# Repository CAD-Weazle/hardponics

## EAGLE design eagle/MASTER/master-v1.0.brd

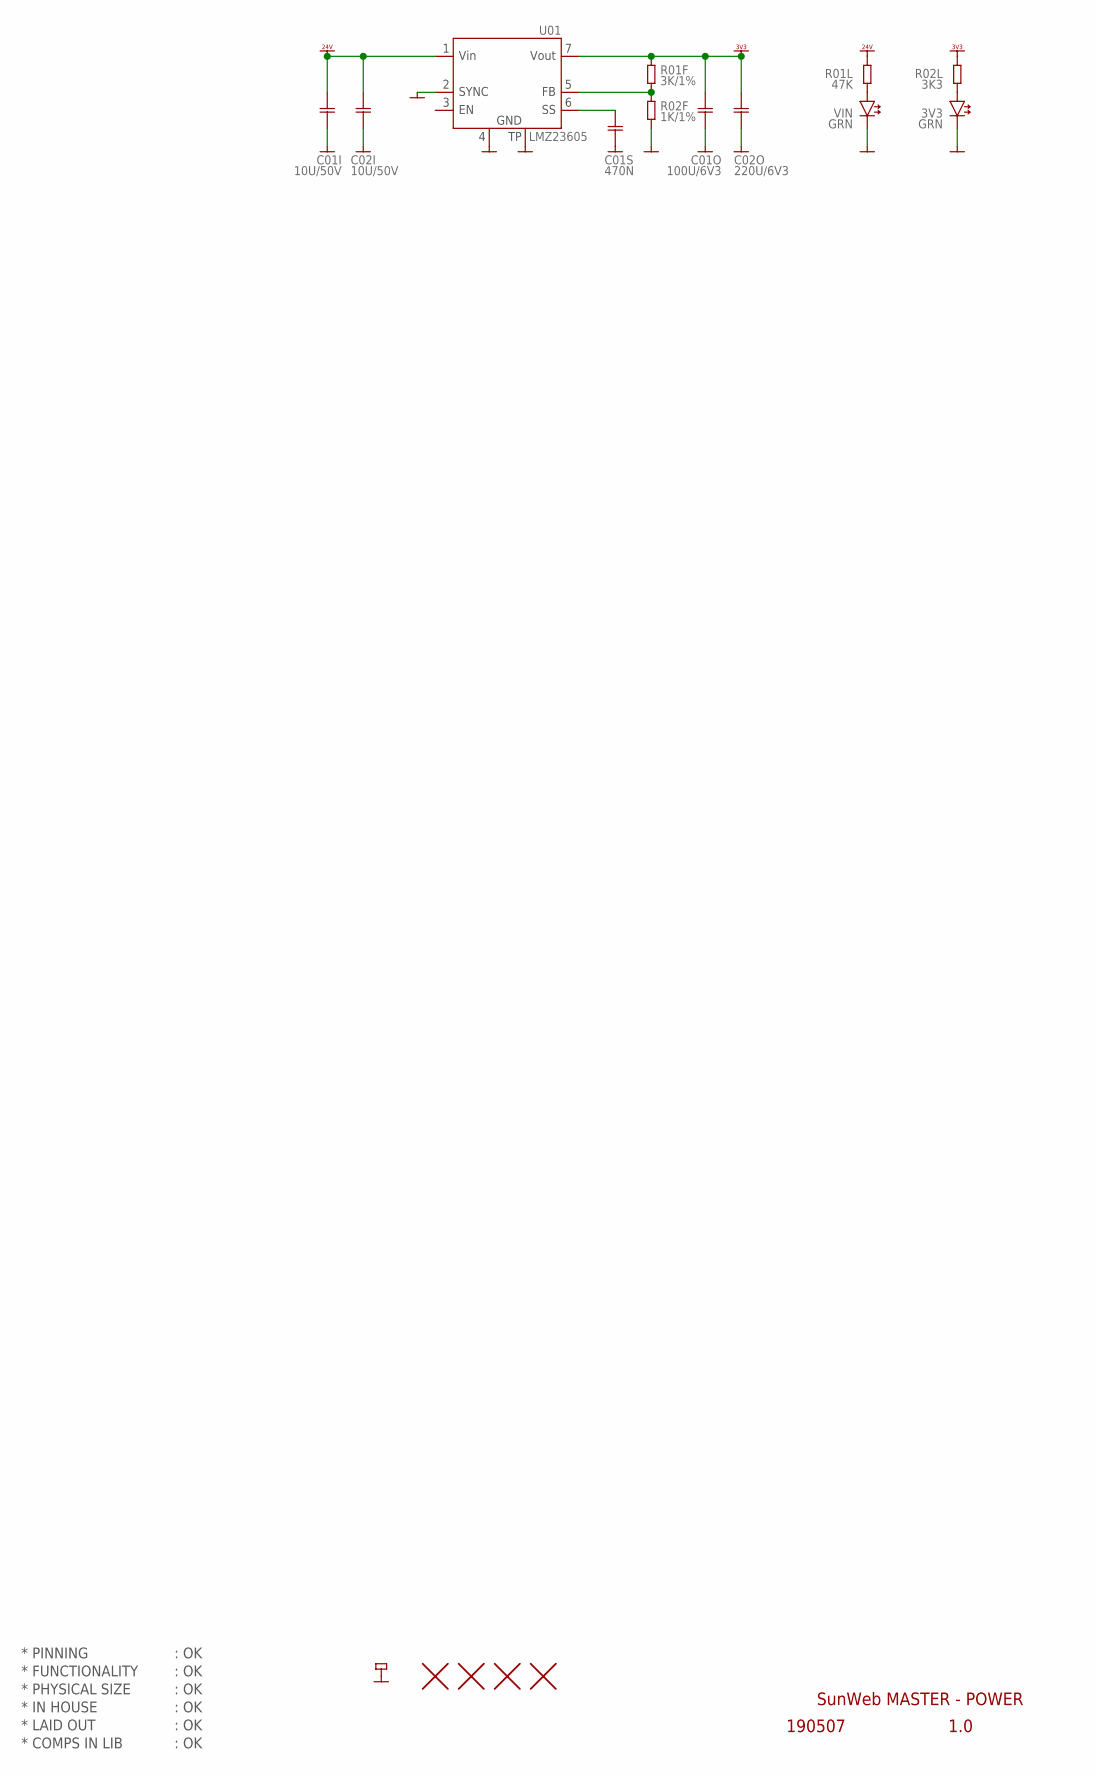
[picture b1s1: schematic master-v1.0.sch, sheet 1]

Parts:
3V3: GRN; LED_SMD_0603
C01I, C02I: 10U/50V; CAP1210
C01O: 100U/6V3; CAP1210
C01S: 470N; CAP0603
C02O: 220U/6V3; CAP2917
H1, H2, H3, H4: HOLE_NPTH_3.2MM
R01F: 3K/1%; RES0603@2
R01L: 47K; RES0603
R02F: 1K/1%; RES0603@2
R02L: 3K3; RES0603
TP2: PIN_GND; HOLE_PTH_1.8MM_SQR
U01: LMZ23605; TOPMOD-7
VIN: GRN; LED_SMD_0603

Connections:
GND: 3V3.C, C01I.2, C01O.2, C01S.2, C02I.2, C02O.2, R02F.1, TP2.1, U01.2 (2.SYNC), U01.4 (4.GND), U01.TP, VIN.C; also elsewhere on the board
unnamed: 3V3.A, R02L.2
unnamed: R01L.2, VIN.A
unnamed: C01S.1, U01.6 (6.SS)
unnamed: R01F.1, R02F.2, U01.5 (5.FB)
VDD_3V3: C01O.1, C02O.1, R01F.2, R02L.1, U01.7 (7.VOUT); also elsewhere on the board
VDD_24V: C01I.1, C02I.1, R01L.1, U01.1 (1.VIN); also elsewhere on the board

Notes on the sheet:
* PINNING
* FUNCTIONALITY
* PHYSICAL SIZE
* LAID OUT
* COMPS IN LIB
* IN HOUSE
SunWeb MASTER - POWER
190507
1.0
: OK

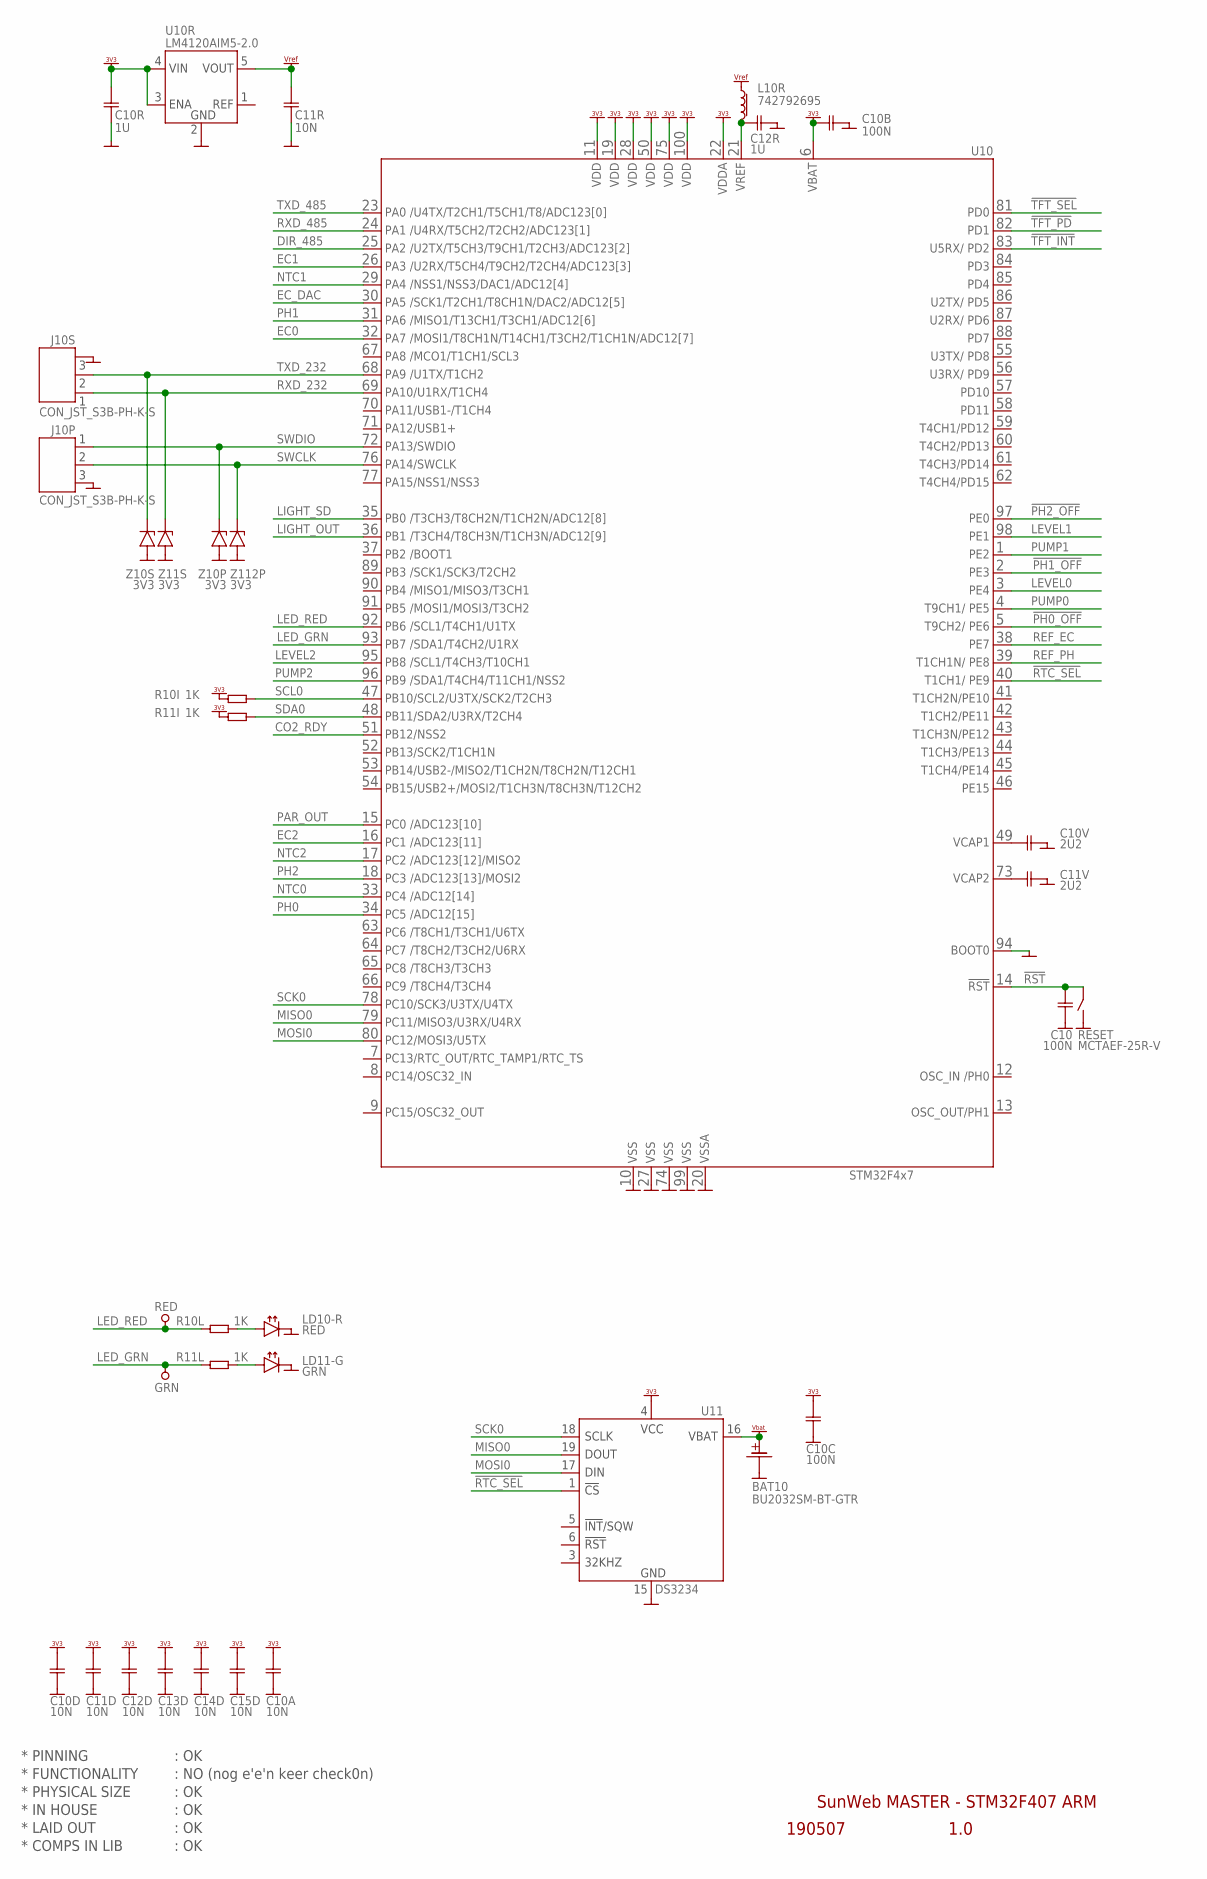
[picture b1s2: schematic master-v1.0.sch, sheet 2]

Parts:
BAT10: BU2032SM-BT-GTR
C10, C10B, C10C: 100N; CAP0603
C10A, C10D, C11D, C11R, C12D, C13D, C14D, C15D: 10N; CAP0603
C10R, C12R: 1U; CAP0603
C10V, C11V: 2U2; CAP0603
GRN: PIN_TEST; HOLE_PTH_0.8MM
J10P, J10S: CON_JST_S3B-PH-K-S
L10R: 742792695; L_0603
LD10-R: RED; LED_SMD_0603
LD11-G: GRN; LED_SMD_0603
R10I, R10L, R11I, R11L: 1K; RES0603
RED: PIN_TEST; HOLE_PTH_0.8MM
RESET: MCTAEF-25R-V; SWITCH_SMD_PBUTTON_2P
U10: STM32F407VG; LQFP100
U10R: LM4120AIM5-2.0; SOT23-5
U11: DS3234; SO20W
Z10P, Z10S, Z11S, Z112P: 3V3; ZENER_SOD80

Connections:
!PH0_OFF: U10.5 (5.PE6); also elsewhere on the board
!PH1_OFF: U10.2 (2.PE3); also elsewhere on the board
!PH2_OFF: U10.97 (97.PE0); also elsewhere on the board
!RST: C10.1, RESET.2 (3-4), U10.14 (14.!RST)
!RTC_SEL: U10.40 (40.PE9), U11.1 (1.CS)
!TFT_INT: U10.83 (83.PD2); also elsewhere on the board
!TFT_PD: U10.82 (82.PD1); also elsewhere on the board
!TFT_SEL: U10.81 (81.PD0); also elsewhere on the board
CO2_RDY: U10.51 (51.PB12); also elsewhere on the board
DIR_485: U10.25 (25.PA2); also elsewhere on the board
EC0: U10.32 (32.PA7); also elsewhere on the board
EC1: U10.26 (26.PA3); also elsewhere on the board
EC2: U10.16 (16.PC1); also elsewhere on the board
EC_DAC: U10.30 (30.PA5); also elsewhere on the board
GND: BAT10.2.- (2), C10.2, C10A.2, C10B.2, C10C.2, C10D.2, C10R.2, C10V.2, C11D.2, C11R.2, C11V.2, C12D.2, C12R.1, C13D.2, C14D.2, C15D.2, J10P.3, J10S.3, LD10-R.C, LD11-G.C, RESET.1 (1-2), U10.10 (10.VSS), U10.20 (20.VSSA), U10.27 (27.VSS), U10.74 (74.VSS), U10.94 (94.BOOT0), U10.99 (99.VSS), U10R.2 (2.GND), U11.2 (15.GND), U11.7 (15.GND), U11.8 (15.GND), U11.9 (15.GND), U11.10 (15.GND), U11.11 (15.GND), U11.12 (15.GND), U11.13 (15.GND), U11.14 (15.GND), U11.15 (15.GND), Z10P.1 (+), Z10S.1 (+), Z11S.1 (+), Z112P.1 (+); also elsewhere on the board
LED_GRN: GRN.1, R11L.1, U10.93 (93.PB7)
LED_RED: R10L.1, RED.1, U10.92 (92.PB6)
LEVEL0: U10.3 (3.PE4); also elsewhere on the board
LEVEL1: U10.98 (98.PE1); also elsewhere on the board
LEVEL2: U10.95 (95.PB8); also elsewhere on the board
LIGHT_OUT: U10.36 (36.PB1); also elsewhere on the board
LIGHT_SD: U10.35 (35.PB0); also elsewhere on the board
MISO0: U10.79 (79.PC11), U11.19 (19.DOUT); also elsewhere on the board
MOSI0: U10.80 (80.PC12), U11.17 (17.DIN); also elsewhere on the board
unnamed: C10V.1, U10.49 (49.VCAP1)
unnamed: C11V.1, U10.73 (73.VCAP2)
unnamed: LD11-G.A, R11L.2
unnamed: LD10-R.A, R10L.2
NTC0: U10.33 (33.PC4); also elsewhere on the board
NTC1: U10.29 (29.PA4); also elsewhere on the board
NTC2: U10.17 (17.PC2); also elsewhere on the board
PAR_OUT: U10.15 (15.PC0); also elsewhere on the board
PH0: U10.34 (34.PC5); also elsewhere on the board
PH1: U10.31 (31.PA6); also elsewhere on the board
PH2: U10.18 (18.PC3); also elsewhere on the board
PUMP0: U10.4 (4.PE5); also elsewhere on the board
PUMP1: U10.1 (1.PE2); also elsewhere on the board
PUMP2: U10.96 (96.PB9); also elsewhere on the board
REF_EC: U10.38 (38.PE7); also elsewhere on the board
REF_PH: U10.39 (39.PE8); also elsewhere on the board
RXD_232: J10S.1, U10.69 (69.PA10), Z11S.2 (-)
RXD_485: U10.24 (24.PA1); also elsewhere on the board
SCK0: U10.78 (78.PC10), U11.18 (18/20.SCLK), U11.20 (18/20.SCLK); also elsewhere on the board
SCL0: R10I.2, U10.47 (47.PB10); also elsewhere on the board
SDA0: R11I.2, U10.48 (48.PB11); also elsewhere on the board
SWCLK: J10P.2, U10.76 (76.PA14), Z112P.2 (-)
SWDIO: J10P.1, U10.72 (72.PA13), Z10P.2 (-)
TXD_232: J10S.2, U10.68 (68.PA9), Z10S.2 (-)
TXD_485: U10.23 (23.PA0); also elsewhere on the board
VBAT: BAT10.1.+ (1), U11.16 (16.VBAT)
VCC_VREF: C11R.1, L10R.1, U10R.5 (5.VOUT); also elsewhere on the board
VDD_3V3: C10A.1, C10B.1, C10C.1, C10D.1, C10R.1, C11D.1, C12D.1, C13D.1, C14D.1, C15D.1, R10I.1, R11I.1, U10.6 (6.VBAT), U10.11 (11.VDD), U10.19 (19.VDD), U10.22 (22.VDDA), U10.28 (28.VDD), U10.50 (50.VDD), U10.75 (75.VDD), U10.100 (100.VDD), U10R.3 (3.ENA), U10R.4 (4.VIN), U11.4 (4.VCC); also elsewhere on the board
VREF1: C12R.2, L10R.2, U10.21 (21.VREF+)

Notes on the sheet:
* PINNING
* FUNCTIONALITY
* PHYSICAL SIZE
* LAID OUT
* COMPS IN LIB
* IN HOUSE
: OK
SunWeb MASTER - STM32F407 ARM
190507
1.0
: NO (nog e'e'n keer check0n)

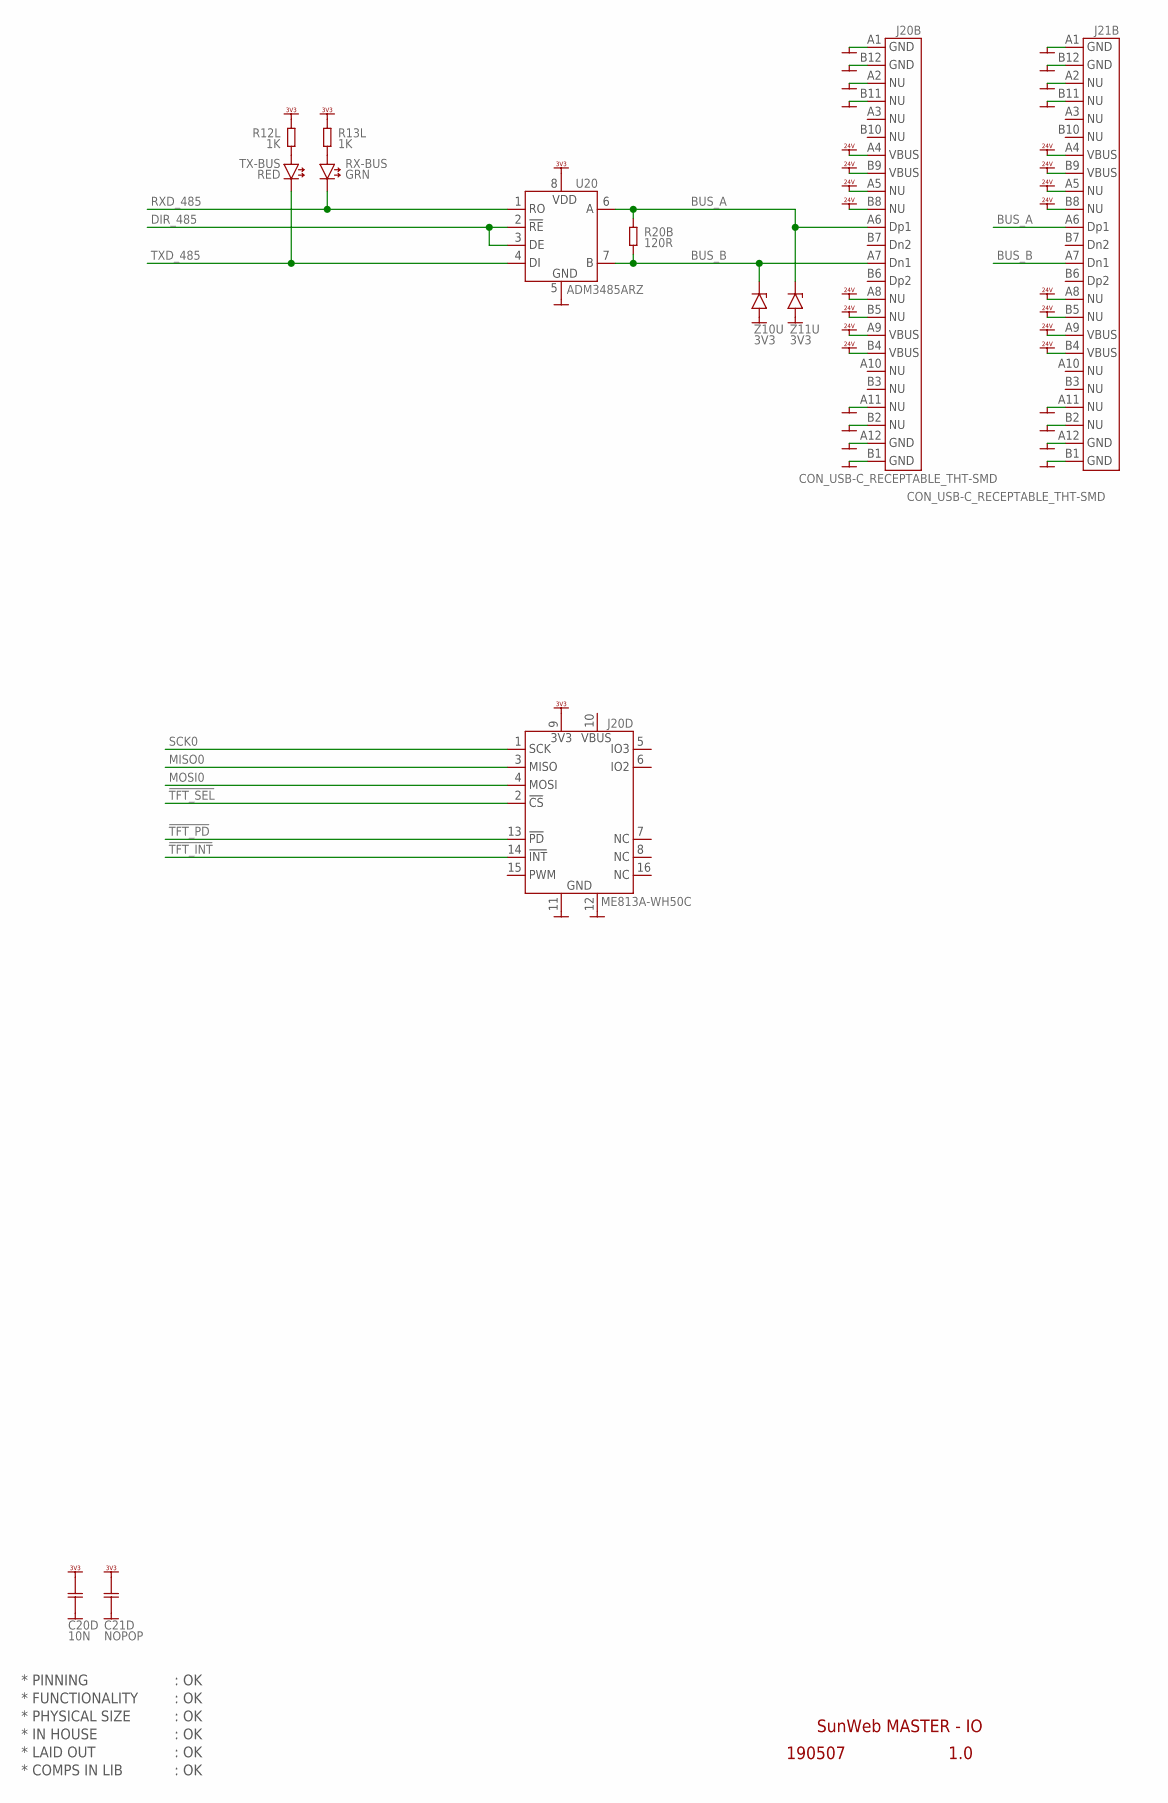
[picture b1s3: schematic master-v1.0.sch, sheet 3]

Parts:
C20D: 10N; CAP0603
C21D: NOPOP; CAP1210
J20B, J21B: CON_USB-C_RECEPTABLE_THT-SMD
J20D: ME813A-WH50C
R12L, R13L: 1K; RES0603
R20B: 120R; RES0603
RX-BUS: GRN; LED_SMD_0603
TX-BUS: RED; LED_SMD_0603
U20: ADM3485ARZ; SO8
Z10U, Z11U: 3V3; ZENER_SOD80

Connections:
!TFT_INT: J20D.14 (14.!INT); also elsewhere on the board
!TFT_PD: J20D.13 (13.!PD); also elsewhere on the board
!TFT_SEL: J20D.2 (2.!CS); also elsewhere on the board
BUS_A: J20B.A6 (A6.DP1), J21B.A6 (A6.DP1), R20B.1, U20.6 (6.A), Z11U.2 (-)
BUS_B: J20B.A7 (A7.DN1), J21B.A7 (A7.DN1), R20B.2, U20.7 (7.B), Z10U.2 (-)
DIR_485: U20.2 (2.!RE), U20.3 (3.DE); also elsewhere on the board
GND: C20D.2, C21D.2, J20B.A1 (A1.GND), J20B.A2 (A2.NU), J20B.A11 (A11.NU), J20B.A12 (A12.GND), J20B.B1 (B1.GND), J20B.B2 (B2.NU), J20B.B11 (B11.NU), J20B.B12 (B12.GND), J20D.11 (11.GND), J20D.12 (12.GND), J21B.A1 (A1.GND), J21B.A2 (A2.NU), J21B.A11 (A11.NU), J21B.A12 (A12.GND), J21B.B1 (B1.GND), J21B.B2 (B2.NU), J21B.B11 (B11.NU), J21B.B12 (B12.GND), U20.5 (5.GND), Z10U.1 (+), Z11U.1 (+); also elsewhere on the board
MISO0: J20D.3 (3.MISO); also elsewhere on the board
MOSI0: J20D.4 (4.MOSI); also elsewhere on the board
unnamed: R13L.2, RX-BUS.A
unnamed: R12L.2, TX-BUS.A
RXD_485: RX-BUS.C, U20.1 (1.RO); also elsewhere on the board
SCK0: J20D.1 (1.SCK); also elsewhere on the board
TXD_485: TX-BUS.C, U20.4 (4.DI); also elsewhere on the board
VDD_3V3: C20D.1, C21D.1, J20D.9 (9.3V3_IN), R12L.1, R13L.1, U20.8 (8.VDD); also elsewhere on the board
VDD_24V: J20B.A4 (A4.VBUS), J20B.A5 (A5.NU), J20B.A8 (A8.NU), J20B.A9 (A9.VBUS), J20B.B4 (B4.VBUS), J20B.B5 (B5.NU), J20B.B8 (B8.NU), J20B.B9 (B9.VBUS), J21B.A4 (A4.VBUS), J21B.A5 (A5.NU), J21B.A8 (A8.NU), J21B.A9 (A9.VBUS), J21B.B4 (B4.VBUS), J21B.B5 (B5.NU), J21B.B8 (B8.NU), J21B.B9 (B9.VBUS); also elsewhere on the board

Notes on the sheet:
* PINNING
* FUNCTIONALITY
* PHYSICAL SIZE
* LAID OUT
* COMPS IN LIB
* IN HOUSE
1.0
SunWeb MASTER - IO
190507
: OK

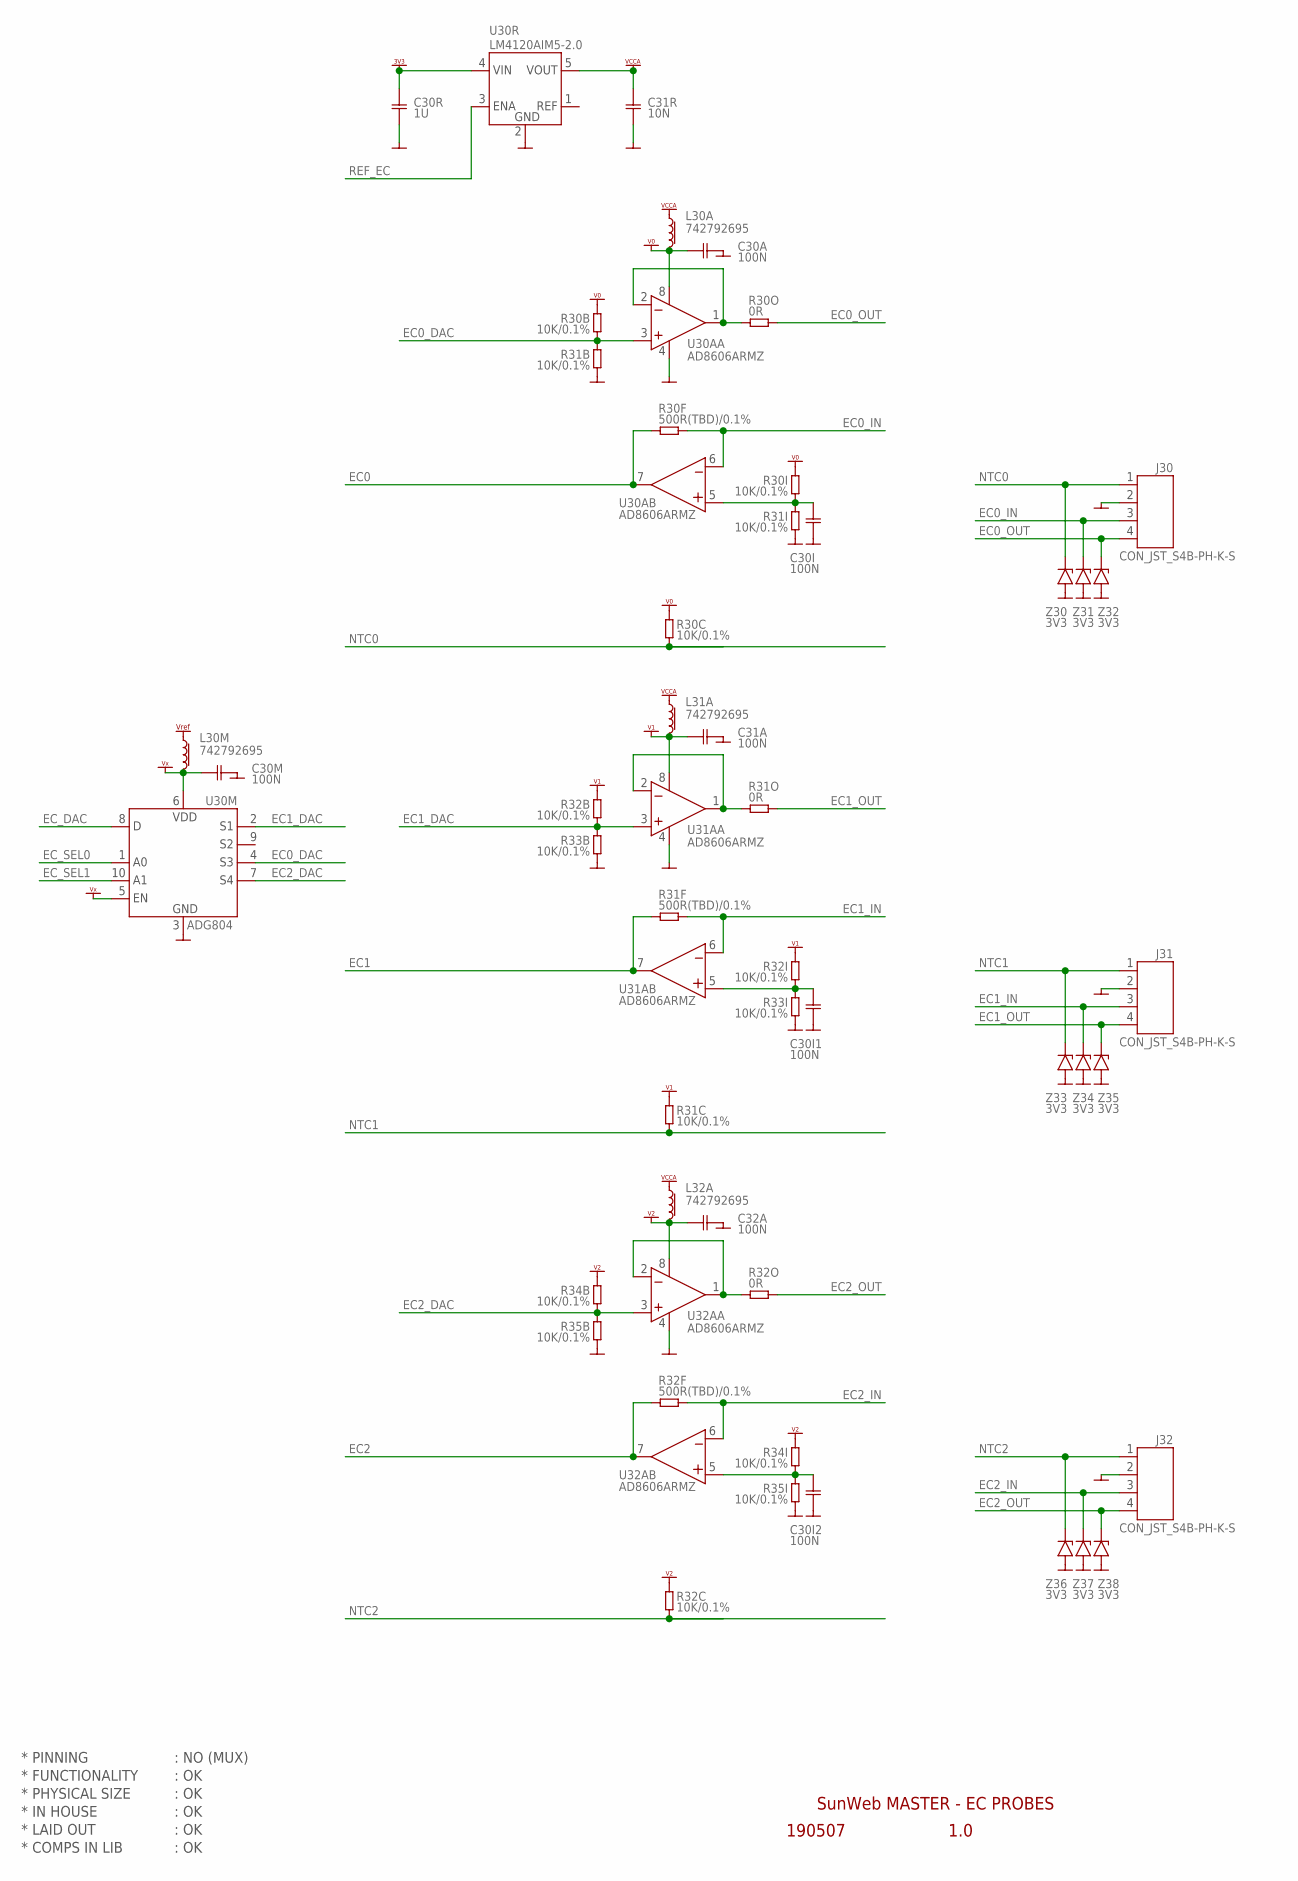
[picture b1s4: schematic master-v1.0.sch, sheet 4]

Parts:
C30A, C30I, C30I1, C30I2, C30M, C31A, C32A: 100N; CAP0603
C30R: 1U; CAP0603
C31R: 10N; CAP0603
J30, J31, J32: CON_JST_S4B-PH-K-S
L30A, L30M, L31A, L32A: 742792695; L_0603
R30B, R30C, R30I, R31B, R31C, R31I, R32B, R32C, R32I, R33B, R33I, R34B, R34I, R35B, R35I: 10K/0.1%; RES0603
R30F, R31F, R32F: 500R(TBD)/0.1%; RES0603
R30O, R31O, R32O: 0R; RES0603
U30A, U31A, U32A: AD8606ARMZ; MSOP8
U30M: ADG804; MSOP10
U30R: LM4120AIM5-2.0; SOT23-5
Z30, Z31, Z32, Z33, Z34, Z35, Z36, Z37, Z38: 3V3; ZENER_SOD80

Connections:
EC0: R30F.2, U30A.8 (7.OUT); also elsewhere on the board
EC0_DAC: R30B.2, R31B.1, U30A.3 (3.IN+), U30M.4 (4.S3)
EC0_IN: J30.3, R30F.1, U30A.7 (6.IN-), Z31.2 (-)
EC0_OUT: J30.4, R30O.1, Z32.2 (-)
EC1: R31F.2, U31A.8 (7.OUT); also elsewhere on the board
EC1_DAC: R32B.2, R33B.1, U30M.2 (2.S1), U31A.3 (3.IN+)
EC1_IN: J31.3, R31F.1, U31A.7 (6.IN-), Z34.2 (-)
EC1_OUT: J31.4, R31O.1, Z35.2 (-)
EC2: R32F.2, U32A.8 (7.OUT); also elsewhere on the board
EC2_DAC: R34B.2, R35B.1, U30M.7 (7.S4), U32A.3 (3.IN+)
EC2_IN: J32.3, R32F.1, U32A.7 (6.IN-), Z37.2 (-)
EC2_OUT: J32.4, R32O.1, Z38.2 (-)
EC30_BUF: R30O.2, U30A.1 (1.OUT), U30A.2 (2.IN-)
EC30_BUF1: R31O.2, U31A.1 (1.OUT), U31A.2 (2.IN-)
EC30_BUF2: R32O.2, U32A.1 (1.OUT), U32A.2 (2.IN-)
EC_DAC: U30M.8 (8.D); also elsewhere on the board
EC_SEL0: U30M.1 (1.A0)
EC_SEL1: U30M.10 (10.A1)
GND: C30A.2, C30I.1, C30I1.1, C30I2.1, C30M.2, C30R.2, C31A.2, C31R.2, C32A.2, J30.2, J31.2, J32.2, R31B.2, R31I.2, R33B.2, R33I.2, R35B.2, R35I.2, U30A.4 (4.V-), U30M.3 (3.GND), U30R.2 (2.GND), U31A.4 (4.V-), U32A.4 (4.V-), Z30.1 (+), Z31.1 (+), Z32.1 (+), Z33.1 (+), Z34.1 (+), Z35.1 (+), Z36.1 (+), Z37.1 (+), Z38.1 (+); also elsewhere on the board
unnamed: C30I1.2, R32I.2, R33I.1, U31A.6 (5.IN+)
unnamed: C30I2.2, R34I.2, R35I.1, U32A.6 (5.IN+)
unnamed: C30I.2, R30I.2, R31I.1, U30A.6 (5.IN+)
NTC0: J30.1, R30C.2, Z30.2 (-); also elsewhere on the board
NTC1: J31.1, R31C.2, Z33.2 (-); also elsewhere on the board
NTC2: J32.1, R32C.2, Z36.2 (-); also elsewhere on the board
REF_EC: U30R.3 (3.ENA); also elsewhere on the board
V0: C30A.1, L30A.2, R30B.1, R30C.1, R30I.1, U30A.5 (8.V+)
V1: C31A.1, L31A.2, R31C.1, R32B.1, R32I.1, U31A.5 (8.V+)
V2: C32A.1, L32A.2, R32C.1, R34B.1, R34I.1, U32A.5 (8.V+)
VCCA: C31R.1, L30A.1, L31A.1, L32A.1, U30R.5 (5.VOUT)
VCC_VREF: L30M.1; also elsewhere on the board
VDD_3V3: C30R.1, U30R.4 (4.VIN); also elsewhere on the board
VX: C30M.1, L30M.2, U30M.5 (5.EN), U30M.6 (6.VDD)

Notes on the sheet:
* PINNING
* FUNCTIONALITY
* PHYSICAL SIZE
* LAID OUT
* COMPS IN LIB
* IN HOUSE
1.0
SunWeb MASTER - EC PROBES
190507
: NO (MUX)
: OK

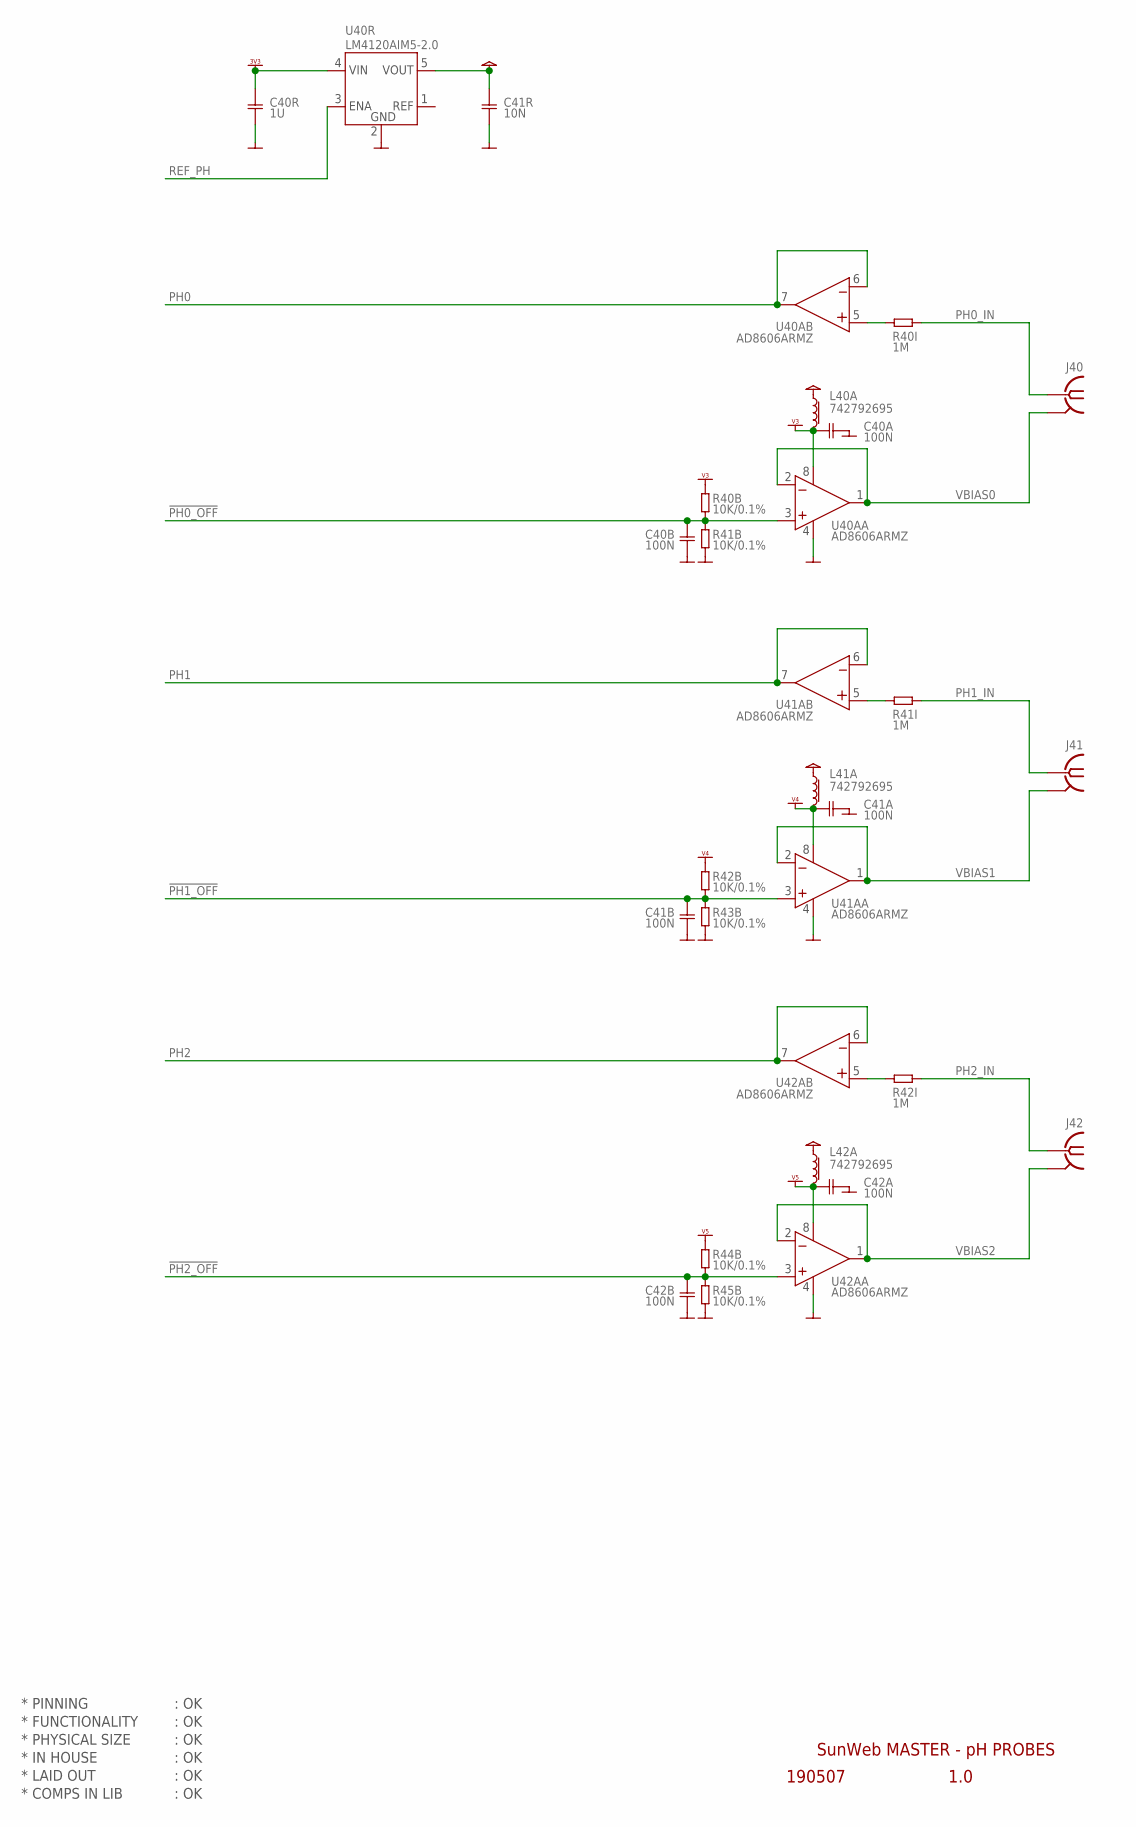
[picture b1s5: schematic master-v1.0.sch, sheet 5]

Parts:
C40A, C40B, C41A, C41B, C42A, C42B: 100N; CAP0603
C40R: 1U; CAP0603
C41R: 10N; CAP0603
J40, J41, J42: CON_SMA_EDGE_PCB_WIDE_4_CPW; SMA_LAUNCH_WIDE_4LAYER_CPW
L40A, L41A, L42A: 742792695; L_0603
R40B, R41B, R42B, R43B, R44B, R45B: 10K/0.1%; RES0603
R40I, R41I, R42I: 1M; RES0603
U40A, U41A, U42A: AD8606ARMZ; MSOP8
U40R: LM4120AIM5-2.0; SOT23-5

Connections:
!PH0_OFF: C40B.2, R40B.2, R41B.1, U40A.3 (3.IN+); also elsewhere on the board
!PH1_OFF: C41B.2, R42B.2, R43B.1, U41A.3 (3.IN+); also elsewhere on the board
!PH2_OFF: C42B.2, R44B.2, R45B.1, U42A.3 (3.IN+); also elsewhere on the board
GND: C40A.1, C40B.1, C40R.2, C41A.1, C41B.1, C41R.2, C42A.1, C42B.1, R41B.2, R43B.2, R45B.2, U40A.4 (4.V-), U40R.2 (2.GND), U41A.4 (4.V-), U42A.4 (4.V-); also elsewhere on the board
unnamed: R41I.2, U41A.6 (5.IN+)
unnamed: R42I.2, U42A.6 (5.IN+)
unnamed: R40I.2, U40A.6 (5.IN+)
PH0: U40A.7 (6.IN-), U40A.8 (7.OUT); also elsewhere on the board
PH0_IN: J40.PIN (1), R40I.1
PH1: U41A.7 (6.IN-), U41A.8 (7.OUT); also elsewhere on the board
PH1_IN: J41.PIN (1), R41I.1
PH2: U42A.7 (6.IN-), U42A.8 (7.OUT); also elsewhere on the board
PH2_IN: J42.PIN (1), R42I.1
REF_PH: U40R.3 (3.ENA); also elsewhere on the board
V3: C40A.2, L40A.2, R40B.1, U40A.5 (8.V+)
V4: C41A.2, L41A.2, R42B.1, U41A.5 (8.V+)
V5: C42A.2, L42A.2, R44B.1, U42A.5 (8.V+)
VBIAS0: J40.GND1 (GND), J40.GND2 (GND), J40.GND3 (GND), J40.GND4 (GND), J40.GND5 (GND), U40A.1 (1.OUT), U40A.2 (2.IN-)
VBIAS1: J41.GND1 (GND), J41.GND2 (GND), J41.GND3 (GND), J41.GND4 (GND), J41.GND5 (GND), U41A.1 (1.OUT), U41A.2 (2.IN-)
VBIAS2: J42.GND1 (GND), J42.GND2 (GND), J42.GND3 (GND), J42.GND4 (GND), J42.GND5 (GND), U42A.1 (1.OUT), U42A.2 (2.IN-)
VCC: C41R.1, L40A.1, L41A.1, L42A.1, U40R.5 (5.VOUT)
VDD_3V3: C40R.1, U40R.4 (4.VIN); also elsewhere on the board

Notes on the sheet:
* PINNING
* FUNCTIONALITY
* PHYSICAL SIZE
* LAID OUT
* COMPS IN LIB
* IN HOUSE
1.0
SunWeb MASTER - pH PROBES
190507
: OK

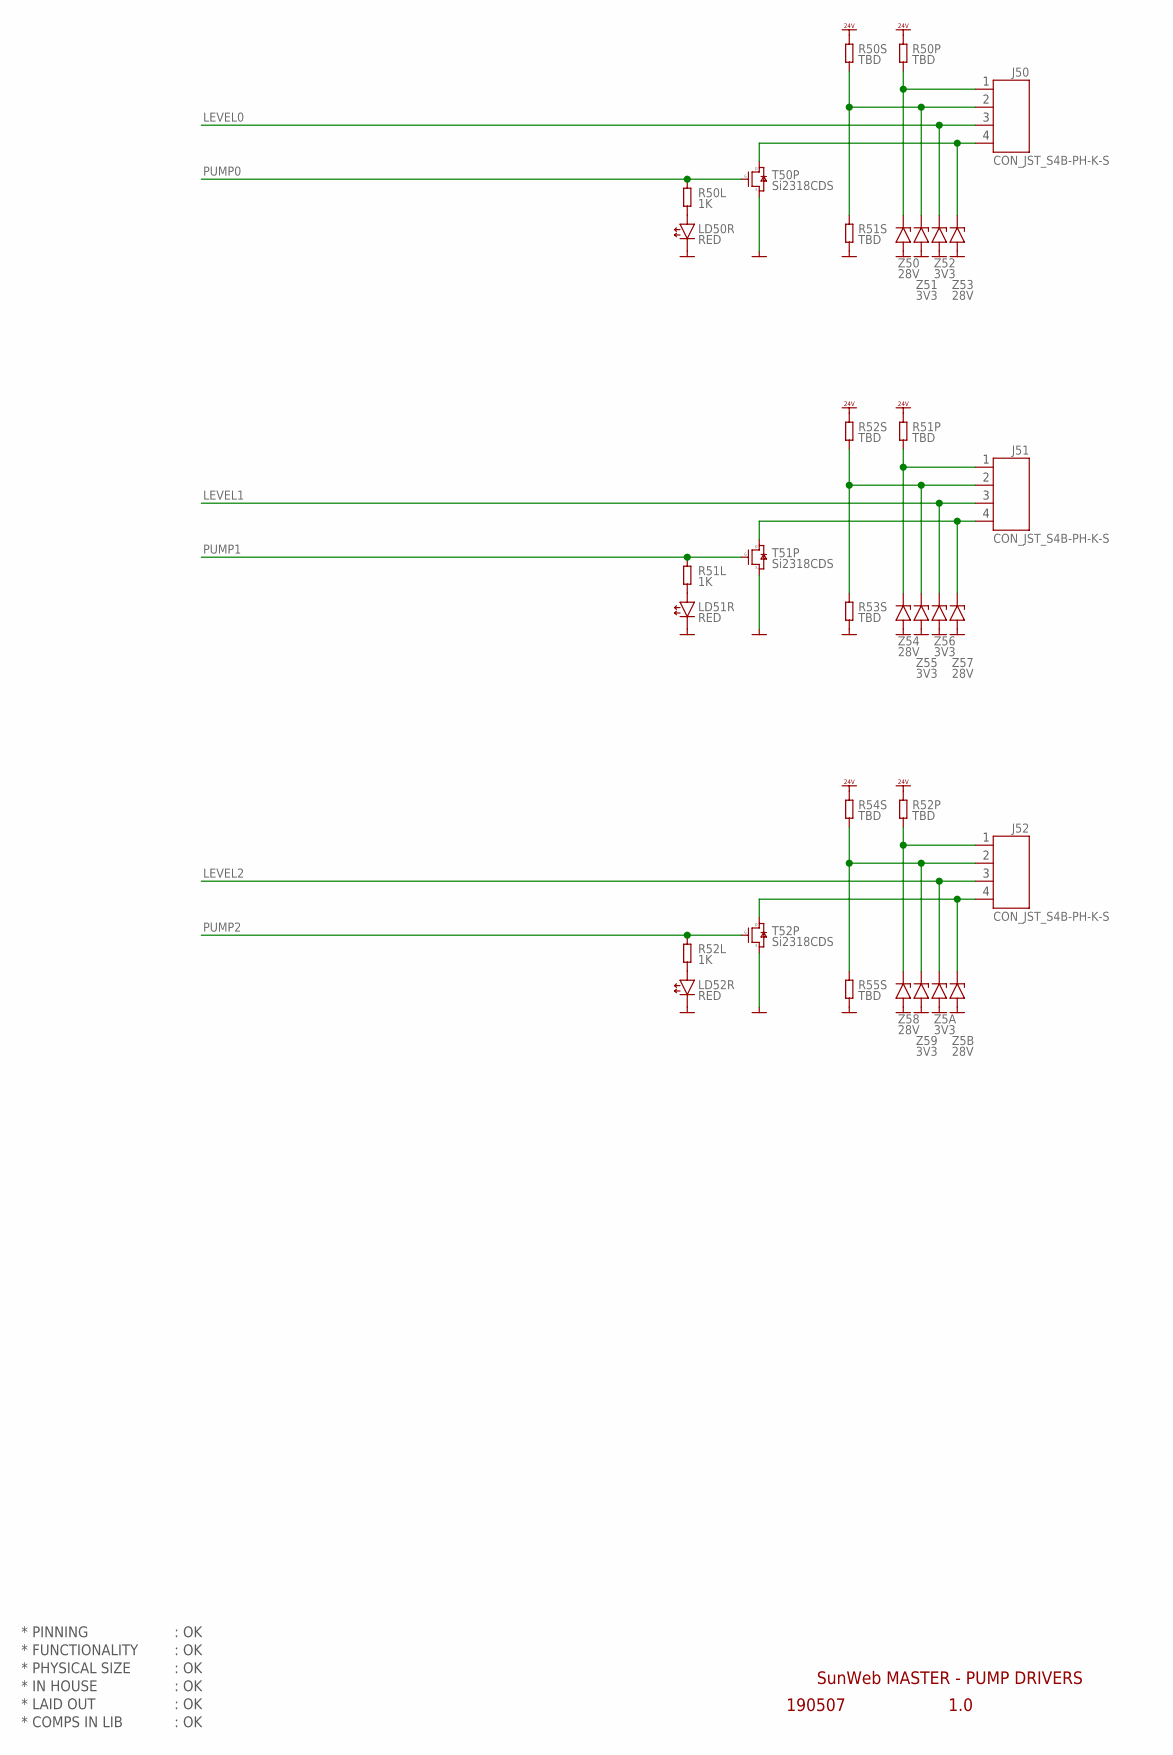
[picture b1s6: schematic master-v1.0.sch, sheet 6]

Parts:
J50, J51, J52: CON_JST_S4B-PH-K-S
LD50R, LD51R, LD52R: RED; LED_SMD_0603
R50L, R51L, R52L: 1K; RES0603
R50P, R51P, R52P: TBD; RES0805
R50S, R51S, R52S, R53S, R54S, R55S: TBD; RES0603
T50P, T51P, T52P: Si2318CDS; NFET_SOT23
Z5A, Z51, Z52, Z55, Z56, Z59: 3V3; ZENER_SOD80
Z5B, Z50, Z53, Z54, Z57, Z58: 28V; ZENER_SOD80

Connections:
GND: LD50R.C, LD51R.C, LD52R.C, R51S.2, R53S.2, R55S.2, T50P.2 (S2), T51P.2 (S2), T52P.2 (S2), Z5A.1 (+), Z5B.1 (+), Z50.1 (+), Z51.1 (+), Z52.1 (+), Z53.1 (+), Z54.1 (+), Z55.1 (+), Z56.1 (+), Z57.1 (+), Z58.1 (+), Z59.1 (+); also elsewhere on the board
LEVEL0: J50.3, Z52.2 (-); also elsewhere on the board
LEVEL1: J51.3, Z56.2 (-); also elsewhere on the board
LEVEL2: J52.3, Z5A.2 (-); also elsewhere on the board
unnamed: J50.1, R50P.2, Z50.2 (-)
unnamed: J50.4, T50P.3 (D3), Z53.2 (-)
unnamed: LD51R.A, R51L.2
unnamed: J50.2, R50S.2, R51S.1, Z51.2 (-)
unnamed: J51.1, R51P.2, Z54.2 (-)
unnamed: J51.4, T51P.3 (D3), Z57.2 (-)
unnamed: J51.2, R52S.2, R53S.1, Z55.2 (-)
unnamed: LD52R.A, R52L.2
unnamed: J52.1, R52P.2, Z58.2 (-)
unnamed: J52.4, T52P.3 (D3), Z5B.2 (-)
unnamed: J52.2, R54S.2, R55S.1, Z59.2 (-)
unnamed: LD50R.A, R50L.2
PUMP0: R50L.1, T50P.1 (G1); also elsewhere on the board
PUMP1: R51L.1, T51P.1 (G1); also elsewhere on the board
PUMP2: R52L.1, T52P.1 (G1); also elsewhere on the board
VDD_24V: R50P.1, R50S.1, R51P.1, R52P.1, R52S.1, R54S.1; also elsewhere on the board

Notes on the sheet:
* PINNING
* FUNCTIONALITY
* PHYSICAL SIZE
* LAID OUT
* COMPS IN LIB
* IN HOUSE
1.0
SunWeb MASTER - PUMP DRIVERS
190507
: OK
